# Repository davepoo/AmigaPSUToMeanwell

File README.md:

# Amiga PSU To Meanwell
KiCad design for a PCB for a board to mount a Meanwell RT50-B PSU inside an external Amiga PSU A300/600 case.

# Known case compatibility:
A300/600 Power Supply - P-No: 391029-02

Its possible that this design also works in the A1200 PSU but i don't have one to verify that.

# A600 PSU Variants

There are 5 variants of the A600 PSU listed in the service manual, I have only tested the -02 variant (UK Plug), but i would imagine that all these other variants are mechanically the same, so would probably work just as well with this adaptor

PSU Part numbers:

* 391329-01
* 391329-02 - UK Plug (240V)
* 391329-03
* 391329-04
* 391329-05

# A500+ PSU possibly is compatible?

From visual appearances (i don't have one to look at in person), it is possible the A500+ PSU might be mechancially identical to the A600 PSU and therefore might also be compatible with this PCB.

PSU Part numbers:

* 321503-01
* 321503-02 - UK Plug (240V)
* 321503-03
* 321503-04
* 321503-05

# Parts
The PCB was designed for these connecters, by any suitable 2.54mm pitch connectors will do the job.

* Molex, KK 254, 6410, 2 Way, 1 Row, Straight PCB Header - https://uk.rs-online.com/web/p/pcb-headers/4838461/
* Molex, KK 254, 6410, 5 Way, 1 Row, Straight PCB Header - https://uk.rs-online.com/web/p/pcb-headers/1707104/

# YouTube
* v1.01 Assembly - https://youtu.be/UummiZiRQis
* v1.01 Changes - https://youtu.be/RRZ41WjXUbk
* Design in KiCad - https://youtu.be/qDFmNK3edf4

# PCBWay 
The v1.01 board is shared on PCBWay where i got the prototypes manufactured 

https://www.pcbway.com/project/shareproject/A600_PSU_to_Meanwell_RT50_B_Adaptor_board.html

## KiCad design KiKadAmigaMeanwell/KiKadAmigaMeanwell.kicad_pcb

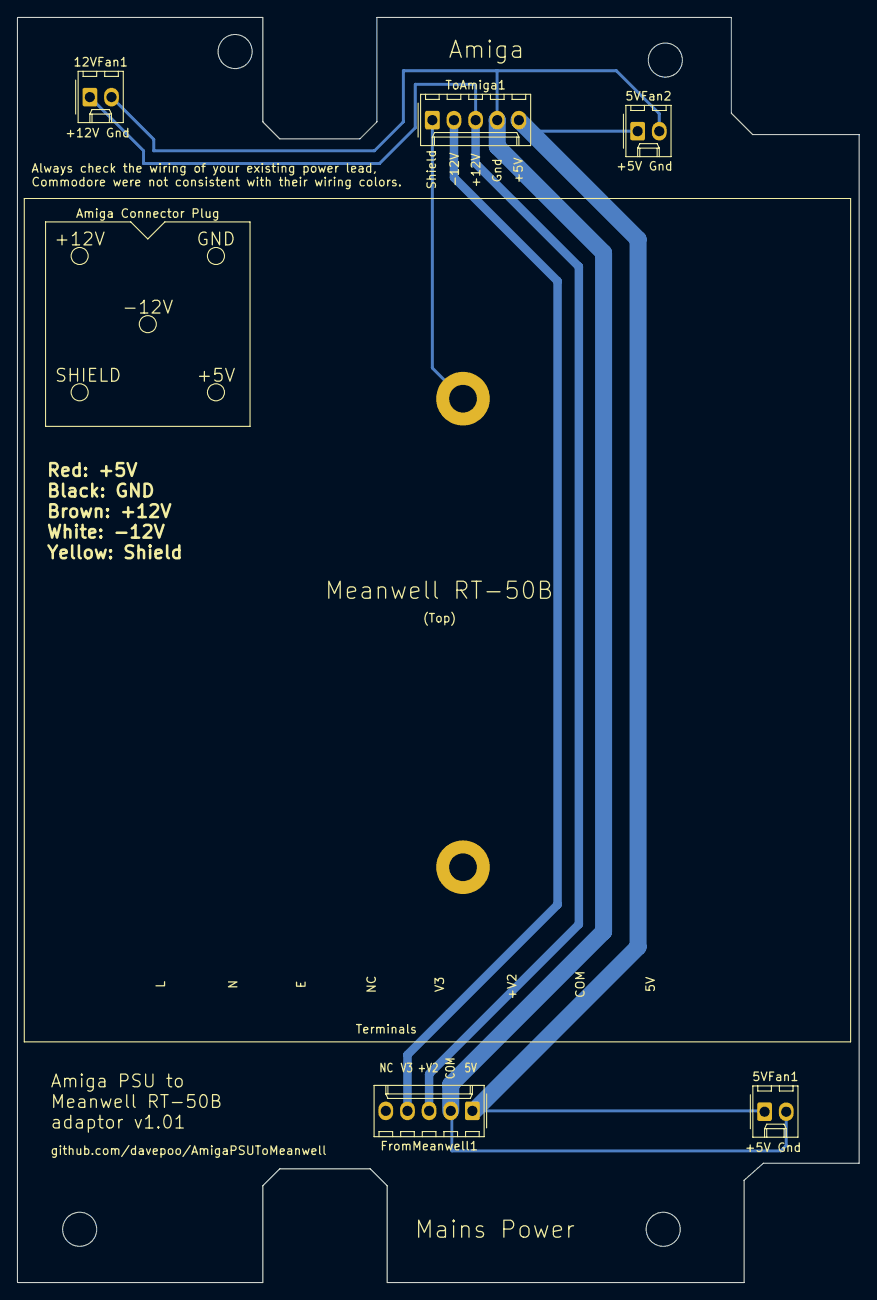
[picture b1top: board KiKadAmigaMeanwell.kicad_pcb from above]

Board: 2 copper layers, 98.8 x 148.5 mm, 11 parts (0 on the bottom side), 4 nets.

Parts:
5VFan1, 5VFan2, 12VFan1: Conn_01x02; Molex_KK-254_AE-6410-02A_1x02_P2.54mm_Vertical
Amiga Connector Plug: AmigaConnector
FromMeanwell1: Conn_01x05; Molex_KK-254_AE-6410-05A_1x05_P2.54mm_Vertical
Meanwell RT-50B: Meanwell_RT50-B
Screw: MountingHole_4mm
Screw#2, Screw#3, Screw#4: MountingHole_4mm
ToAmiga1: Conn_01x05; Molex_KK-254_AE-6410-05A_1x05_P2.54mm_Vertical

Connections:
+5V: 5VFan1.1, 5VFan2.1, FromMeanwell1.1, ToAmiga1.5
+12V: 12VFan1.1, FromMeanwell1.3, ToAmiga1.3
-12V: FromMeanwell1.4, ToAmiga1.2
GND: 5VFan1.2, 5VFan2.2, 12VFan1.2, FromMeanwell1.2, ToAmiga1.4

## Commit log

2020-08-06 - adding KiCad files and Gerbers for v1.00
2020-08-14 - changing out the connectors to Molex KK 5 pin connectors / adding 5V/12V fan headers (not connected yet)
2020-08-14 - adding schematic, and routing the tracks for the connectors and fan headers on the PCB
2020-08-15 - connecting the shield pin to earth instead of ground, making smaller trace widths for the fan headers (0.5A)
2020-08-15 - adding a second 5V fan header
2020-08-15 - adjusting edge cuts to fit around the plastic standoffs
2020-08-15 - adding voltage and ground silkscreen to the fan headers
2020-08-15 - adding render of Front & Back of v1.01
2020-08-15 - updating readme with new render
2020-08-16 - taking 0.2mm off the left hand edge cut & correcting silkscreen errors
2020-08-16 - Gerber files for v1.01
2020-08-22 - adding youtube video links
2020-08-23 - fixing line breaks
2020-08-29 A600/A500+ compatiblity readme changes
    - adding notes about A600 PSU variant compatibility and possible A500+ PSU compatibility
2020-08-29 PCBWay project links
2020-08-30 adding latest youtube video link
